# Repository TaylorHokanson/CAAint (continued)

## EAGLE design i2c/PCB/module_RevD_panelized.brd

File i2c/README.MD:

### Attiny Breakout Hello World

1. Populate breakout board with components:

   - Attiny85
   - 2 x 3mm LEDs
   - 2 x 270ohm resistors
   - male pin headers
   - [.1 uf capacitor](https://www.mouser.com/ProductDetail/Murata-Electronics/RDER71H104K0P1H03B?qs=sGAEpiMZZMukHu%252bjC5l7YWXRuVs7xNwsPrUM%2fIYCMaY%3d) <-- important!
2. Attach [AVR programmer](https://www.sparkfun.com/products/9825) to breakout (taking careful note of plug polarity, see breakout silkscreen for orientation).
3. Select "power device" on programmer via switch.
4. Connect programmer to computer via USB
5. Download and install [board definitions](https://github.com/damellis/attiny) for Attiny
6. Set the following in the Arduino IDE Tools menu:

   - Board: Attiny 25/45/85
   - Processor: Attiny85
   - Clock: 1Mhz
   - Port: Leave this blank
   - Programmer: USBTinyISP
7. Arduino IDE > Tools > Burn Bootloader

   - Only needs to be done once per chip
8. Change Clock to 8mhz internal.
8. Upload [attiny_hello_world.ino](Code/) with the same settings as above.
9. If all goes well, this will flash the second LED on the breakout.

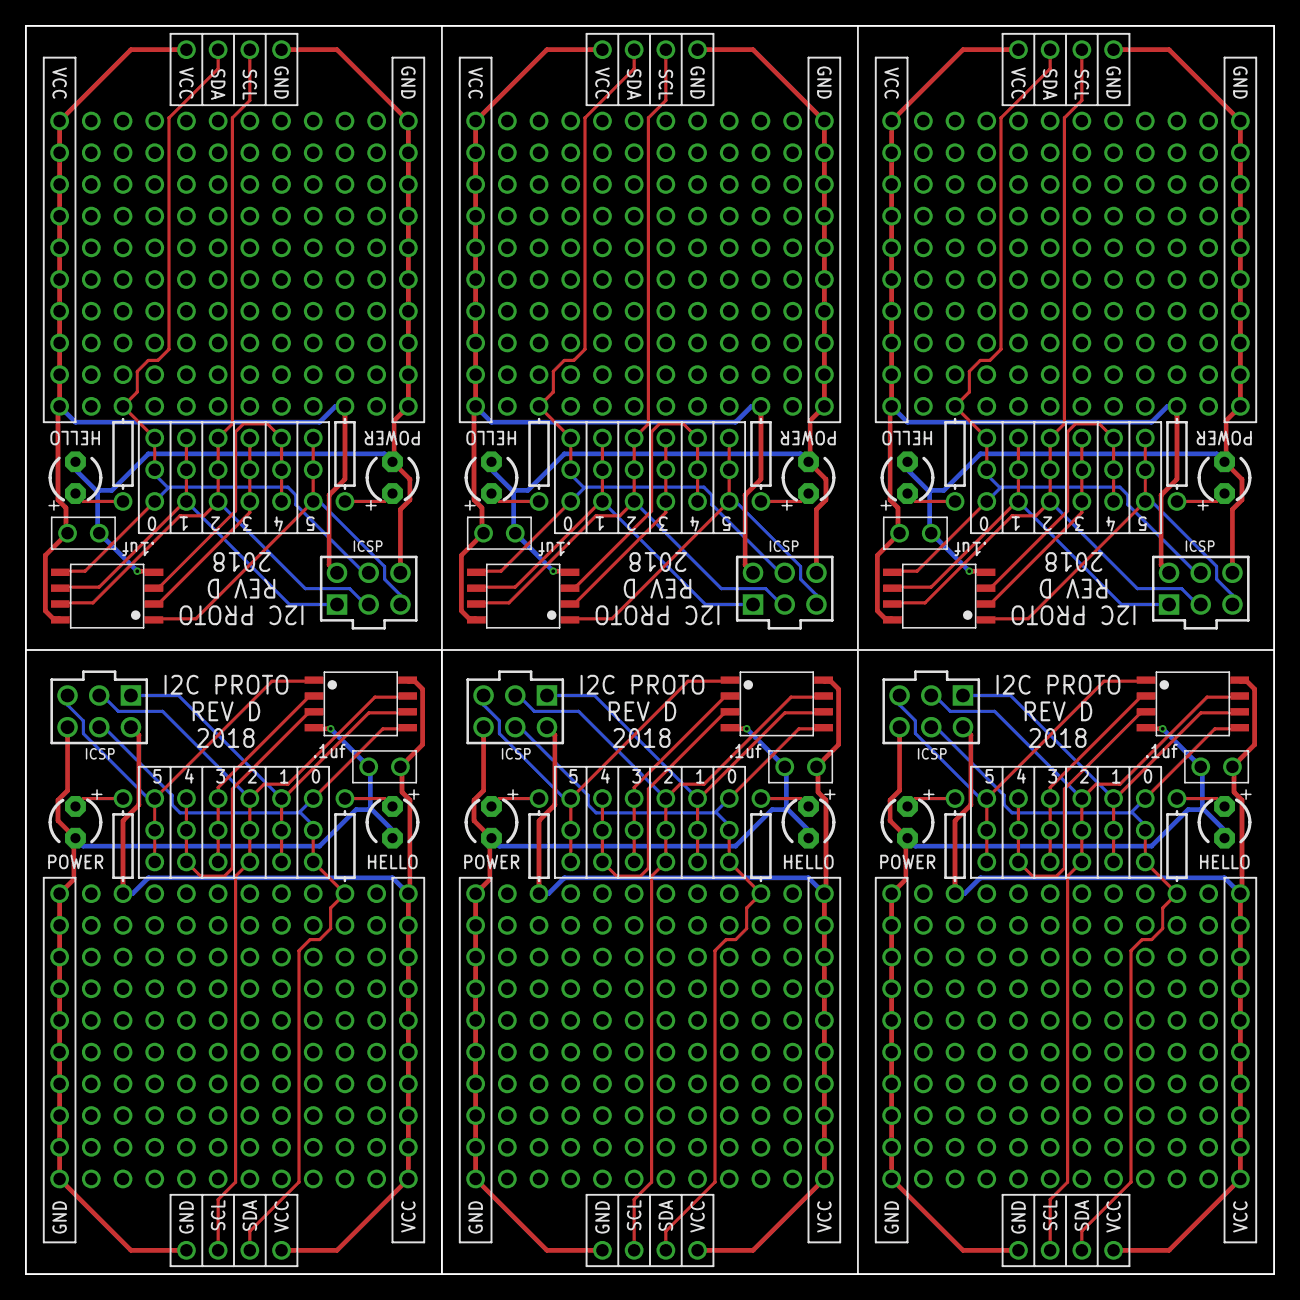
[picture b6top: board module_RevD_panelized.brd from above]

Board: 2 copper layers, 100.0 x 100.0 mm, 882 parts (0 on the bottom side), 60 nets.

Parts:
HELLO, HELLO1, HELLO2, HELLO3, HELLO4, HELLO5: LED3MM
IC1, IC2, IC3, IC4, IC5, IC6: ATTINY85-20SU; SOT127P798X216-8N
J1, J2, J3, J4, J5, J6: M20-9980346; HDRV6W64P254_2X3_762X508X868P
POWER, POWER1, POWER2, POWER3, POWER4, POWER5: LED3MM
U$1, U$2, U$3, U$4, U$5, U$6, U$7, U$8, U$9, U$10, U$11, U$12, U$13, U$14, U$15, U$16, U$17, U$18, U$19, U$20, U$21, U$22, U$23, U$24, U$25, U$26, U$27, U$28, U$29, U$30, U$31, U$32, U$33, U$34, U$35, U$36, U$37, U$38, U$39, U$40, U$41, U$42, U$43, U$44, U$45, U$46, U$47, U$48, U$49, U$50, U$51, U$52, U$53, U$54, U$55, U$56, U$57, U$58, U$59, U$60, U$61, U$62, U$63, U$64, U$65, U$66, U$67, U$68, U$69, U$70, U$75, U$76, U$77, U$78, U$79, U$80, U$81, U$82, U$83, U$84, U$85, U$86, U$87, U$88, U$89, U$90, U$91, U$92, U$93, U$94, U$95, U$96, U$97, U$98, U$99, U$100, U$101, U$102, U$103, U$104, U$105, U$106, U$107, U$108, U$109, U$110, U$111, U$112, U$113, U$114, U$115, U$116, U$117, U$118, U$119, U$120, U$121, U$122, U$124, U$125, U$128, U$129, U$130, U$131, U$132, U$133, U$134, U$135, U$136, U$137, U$138, U$139, U$140, U$141, U$142, U$143, U$144, U$145, U$146, U$147, U$148, U$149, U$150, U$151, U$152, U$153, U$154, U$155, U$156, U$157, U$158, U$159, U$160, U$161, U$162, U$163, U$164, U$165, U$166, U$167, U$168, U$169, U$170, U$171, U$172, U$173, U$174, U$175, U$176, U$177, U$178, U$179, U$180, U$181, U$182, U$183, U$184, U$185, U$186, U$187, U$188, U$189, U$190, U$191, U$192, U$193, U$194, U$195, U$196, U$197, U$198, U$199, U$200, U$201, U$202, U$203, U$204, U$205, U$206, U$207, U$208, U$209, U$210, U$211, U$212, U$213, U$218, U$219, U$220, U$221, U$222, U$223, U$224, U$225, U$226, U$227, U$228, U$229, U$230, U$231, U$232, U$233, U$234, U$235, U$236, U$237, U$238, U$239, U$240, U$241, U$242, U$243, U$244, U$245, U$246, U$247, U$248, U$249, U$250, U$251, U$252, U$253, U$254, U$255, U$256, U$257, U$258, U$259, U$260, U$261, U$262, U$263, U$267, U$268, U$269, U$270, U$271, U$272, U$273, U$274, U$275, U$276, U$277, U$278, U$279, U$280, U$281, U$282, U$283, U$284, U$285, U$286, U$287, U$288, U$289, U$290, U$291, U$292, U$293, U$294, U$295, U$296, U$297, U$298, U$299, U$300, U$301, U$302, U$303, U$304, U$305, U$306, U$307, U$308, U$309, U$310, U$311, U$312, U$313, U$314, U$315, U$316, U$317, U$318, U$319, U$320, U$321, U$322, U$323, U$324, U$325, U$326, U$327, U$328, U$329, U$330, U$331, U$332, U$333, U$334, U$335, U$336, U$337, U$338, U$339, U$340, U$341, U$342, U$343, U$344, U$345, U$346, U$347, U$348, U$349, U$350, U$351, U$352, U$353, U$354, U$355, U$356, U$361, U$362, U$363, U$364, U$365, U$366, U$367, U$368, U$369, U$370, U$371, U$372, U$373, U$374, U$375, U$376, U$377, U$378, U$379, U$380, U$381, U$382, U$383, U$384, U$385, U$386, U$387, U$388, U$389, U$390, U$391, U$392, U$393, U$394, U$395, U$396, U$397, U$398, U$399, U$400, U$401, U$402, U$403, U$404, U$405, U$406, U$410, U$411, U$412, U$413, U$414, U$415, U$416, U$417, U$418, U$419, U$420, U$421, U$422, U$423, U$424, U$425, U$426, U$427, U$428, U$429, U$430, U$431, U$432, U$433, U$434, U$435, U$436, U$437, U$438, U$439, U$440, U$441, U$442, U$443, U$444, U$445, U$446, U$447, U$448, U$449, U$450, U$451, U$452, U$453, U$454, U$455, U$456, U$457, U$458, U$459, U$460, U$461, U$462, U$463, U$464, U$465, U$466, U$467, U$468, U$469, U$470, U$471, U$472, U$473, U$474, U$475, U$476, U$477, U$478, U$479, U$480, U$481, U$482, U$483, U$484, U$485, U$486, U$487, U$488, U$489, U$490, U$491, U$492, U$493, U$494, U$495, U$496, U$497, U$498, U$499, U$504, U$505, U$506, U$507, U$508, U$509, U$510, U$511, U$512, U$513, U$514, U$515, U$516, U$517, U$518, U$519, U$520, U$521, U$522, U$523, U$524, U$525, U$526, U$527, U$528, U$529, U$530, U$531, U$532, U$533, U$534, U$535, U$536, U$537, U$538, U$539, U$540, U$541, U$542, U$543, U$544, U$545, U$546, U$547, U$548, U$549, U$553, U$554, U$555, U$556, U$557, U$558, U$559, U$560, U$561, U$562, U$563, U$564, U$565, U$566, U$567, U$568, U$569, U$570, U$571, U$572, U$573, U$574, U$575, U$576, U$577, U$578, U$579, U$580, U$581, U$582, U$583, U$584, U$585, U$586, U$587, U$588, U$589, U$590, U$591, U$592, U$593, U$594, U$595, U$596, U$597, U$598, U$599, U$600, U$601, U$602, U$603, U$604, U$605, U$606, U$607, U$608, U$609, U$610, U$611, U$612, U$613, U$614, U$615, U$616, U$617, U$618, U$619, U$620, U$621, U$622, U$623, U$624, U$625, U$626, U$627, U$628, U$629, U$630, U$631, U$632, U$633, U$634, U$635, U$636, U$637, U$638, U$639, U$640, U$641, U$642, U$647, U$648, U$649, U$650, U$651, U$652, U$653, U$654, U$655, U$656, U$657, U$658, U$659, U$660, U$661, U$662, U$663, U$664, U$665, U$666, U$667, U$668, U$669, U$670, U$671, U$672, U$673, U$674, U$675, U$676, U$677, U$678, U$679, U$680, U$681, U$682, U$683, U$684, U$685, U$686, U$687, U$688, U$689, U$690, U$691, U$692, U$696, U$697, U$698, U$699, U$700, U$701, U$702, U$703, U$704, U$705, U$706, U$707, U$708, U$709, U$710, U$711, U$712, U$713, U$714, U$715, U$716, U$717, U$718, U$719, U$720, U$721, U$722, U$723, U$724, U$725, U$726, U$727, U$728, U$729, U$730, U$731, U$732, U$733, U$734, U$735, U$736, U$737, U$738, U$739, U$740, U$741, U$742, U$743, U$744, U$745, U$746, U$747, U$748, U$749, U$750, U$751, U$752, U$753, U$754, U$755, U$756, U$757, U$758, U$759, U$760, U$761, U$762, U$763, U$764, U$765, U$766, U$767, U$768, U$769, U$770, U$771, U$772, U$773, U$774, U$775, U$776, U$777, U$778, U$779, U$780, U$781, U$782, U$783, U$784, U$785, U$790, U$791, U$792, U$793, U$794, U$795, U$796, U$797, U$798, U$799, U$800, U$801, U$802, U$803, U$804, U$805, U$806, U$807, U$808, U$809, U$810, U$811, U$812, U$813, U$814, U$815, U$816, U$817, U$818, U$819, U$820, U$821, U$822, U$823, U$824, U$825, U$826, U$827, U$828, U$829, U$830, U$831, U$832, U$833, U$834, U$835, U$839, U$840, U$841, U$842, U$843, U$844, U$845, U$846, U$847, U$848, U$849, U$850, U$851, U$852, U$853, U$854, U$855, U$856, U$857, U$858: ONE_PAD; 1X01
U$71, U$214, U$357, U$500, U$643, U$786: GND; 1X01
U$72, U$216, U$359, U$502, U$645, U$788: SDA; 1X01
U$73, U$217, U$360, U$503, U$646, U$789: SCL; 1X01
U$74, U$215, U$358, U$501, U$644, U$787: VCC; 1X01
U$123, U$264, U$407, U$550, U$693, U$836: DECOUPLING_CAP
U$126, U$127, U$265, U$266, U$408, U$409, U$551, U$552, U$694, U$695, U$837, U$838: RESISTOR; AXIAL-0.3

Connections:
GND: HELLO.NEG, IC1.GND, J1.GND, POWER.NEG, U$71.P$1, U$99.P$1, U$100.P$1, U$123.P$1, U$124.P$1, U$125.P$1, U$128.P$1, U$129.P$1, U$130.P$1, U$131.P$1, U$132.P$1, U$133.P$1
GND1: HELLO1.NEG, IC2.GND, J2.GND, POWER1.NEG, U$214.P$1, U$264.P$1, U$267.P$1, U$268.P$1, U$269.P$1, U$270.P$1, U$271.P$1, U$272.P$1, U$273.P$1, U$274.P$1, U$275.P$1, U$276.P$1
GND2: HELLO2.NEG, IC3.GND, J3.GND, POWER2.NEG, U$357.P$1, U$407.P$1, U$410.P$1, U$411.P$1, U$412.P$1, U$413.P$1, U$414.P$1, U$415.P$1, U$416.P$1, U$417.P$1, U$418.P$1, U$419.P$1
GND3: HELLO3.NEG, IC4.GND, J4.GND, POWER3.NEG, U$500.P$1, U$550.P$1, U$553.P$1, U$554.P$1, U$555.P$1, U$556.P$1, U$557.P$1, U$558.P$1, U$559.P$1, U$560.P$1, U$561.P$1, U$562.P$1
GND6: HELLO4.NEG, IC5.GND, J5.GND, POWER4.NEG, U$643.P$1, U$693.P$1, U$696.P$1, U$697.P$1, U$698.P$1, U$699.P$1, U$700.P$1, U$701.P$1, U$702.P$1, U$703.P$1, U$704.P$1, U$705.P$1
GND7: HELLO5.NEG, IC6.GND, J6.GND, POWER5.NEG, U$786.P$1, U$836.P$1, U$839.P$1, U$840.P$1, U$841.P$1, U$842.P$1, U$843.P$1, U$844.P$1, U$845.P$1, U$846.P$1, U$847.P$1, U$848.P$1
unnamed: POWER.POS, U$126.P$3
unnamed: HELLO.POS, U$127.P$3
unnamed: POWER1.POS, U$265.P$3
unnamed: HELLO1.POS, U$266.P$3
unnamed: POWER2.POS, U$408.P$3
unnamed: HELLO2.POS, U$409.P$3
unnamed: POWER3.POS, U$551.P$3
unnamed: HELLO3.POS, U$552.P$3
unnamed: POWER4.POS, U$694.P$3
unnamed: HELLO4.POS, U$695.P$3
unnamed: POWER5.POS, U$837.P$3
unnamed: HELLO5.POS, U$838.P$3
PB0: IC1.PB0, J1.0/MOSI/SDA, U$72.P$1, U$75.P$1, U$76.P$1, U$77.P$1, U$127.P$4
PB1: IC1.PB1, J1.1/MISO, U$78.P$1, U$79.P$1, U$80.P$1
PB2: IC1.PB2, J1.2/SCK/SCL, U$73.P$1, U$81.P$1, U$82.P$1, U$83.P$1
PB3: IC1.PB3, U$84.P$1, U$85.P$1, U$86.P$1
PB4: IC1.PB4, U$87.P$1, U$88.P$1, U$89.P$1
PB5: IC1.PB5, J1.5/RST, U$90.P$1, U$91.P$1, U$92.P$1
PB6: IC2.PB0, J2.0/MOSI/SDA, U$216.P$1, U$218.P$1, U$219.P$1, U$220.P$1, U$266.P$4
PB7: IC2.PB3, U$227.P$1, U$228.P$1, U$229.P$1
PB8: IC2.PB4, U$230.P$1, U$231.P$1, U$232.P$1
PB9: IC2.PB2, J2.2/SCK/SCL, U$217.P$1, U$224.P$1, U$225.P$1, U$226.P$1
PB10: IC2.PB5, J2.5/RST, U$233.P$1, U$234.P$1, U$235.P$1
PB11: IC2.PB1, J2.1/MISO, U$221.P$1, U$222.P$1, U$223.P$1
PB12: IC3.PB0, J3.0/MOSI/SDA, U$359.P$1, U$361.P$1, U$362.P$1, U$363.P$1, U$409.P$4
PB13: IC3.PB3, U$370.P$1, U$371.P$1, U$372.P$1
PB14: IC3.PB4, U$373.P$1, U$374.P$1, U$375.P$1
PB15: IC3.PB2, J3.2/SCK/SCL, U$360.P$1, U$367.P$1, U$368.P$1, U$369.P$1
PB16: IC3.PB5, J3.5/RST, U$376.P$1, U$377.P$1, U$378.P$1
PB17: IC3.PB1, J3.1/MISO, U$364.P$1, U$365.P$1, U$366.P$1
PB18: IC4.PB0, J4.0/MOSI/SDA, U$502.P$1, U$504.P$1, U$505.P$1, U$506.P$1, U$552.P$4
PB19: IC4.PB3, U$513.P$1, U$514.P$1, U$515.P$1
PB20: IC4.PB4, U$516.P$1, U$517.P$1, U$518.P$1
PB21: IC4.PB2, J4.2/SCK/SCL, U$503.P$1, U$510.P$1, U$511.P$1, U$512.P$1
PB22: IC4.PB5, J4.5/RST, U$519.P$1, U$520.P$1, U$521.P$1
PB23: IC4.PB1, J4.1/MISO, U$507.P$1, U$508.P$1, U$509.P$1
PB24: IC5.PB0, J5.0/MOSI/SDA, U$645.P$1, U$647.P$1, U$648.P$1, U$649.P$1, U$695.P$4
PB25: IC5.PB3, U$656.P$1, U$657.P$1, U$658.P$1
PB26: IC5.PB4, U$659.P$1, U$660.P$1, U$661.P$1
PB27: IC5.PB2, J5.2/SCK/SCL, U$646.P$1, U$653.P$1, U$654.P$1, U$655.P$1
PB30: IC5.PB5, J5.5/RST, U$662.P$1, U$663.P$1, U$664.P$1
PB31: IC5.PB1, J5.1/MISO, U$650.P$1, U$651.P$1, U$652.P$1
PB32: IC6.PB0, J6.0/MOSI/SDA, U$788.P$1, U$790.P$1, U$791.P$1, U$792.P$1, U$838.P$4
PB33: IC6.PB3, U$799.P$1, U$800.P$1, U$801.P$1
PB36: IC6.PB4, U$802.P$1, U$803.P$1, U$804.P$1
PB37: IC6.PB2, J6.2/SCK/SCL, U$789.P$1, U$796.P$1, U$797.P$1, U$798.P$1
PB38: IC6.PB5, J6.5/RST, U$805.P$1, U$806.P$1, U$807.P$1
PB39: IC6.PB1, J6.1/MISO, U$793.P$1, U$794.P$1, U$795.P$1
VCC: IC1.VCC, J1.VCC, U$74.P$1, U$123.P$2, U$126.P$4, U$134.P$1, U$135.P$1, U$136.P$1, U$137.P$1, U$138.P$1, U$139.P$1, U$140.P$1, U$141.P$1, U$142.P$1, U$143.P$1
VCC1: IC2.VCC, J2.VCC, U$215.P$1, U$264.P$2, U$265.P$4, U$277.P$1, U$278.P$1, U$279.P$1, U$280.P$1, U$281.P$1, U$282.P$1, U$283.P$1, U$284.P$1, U$285.P$1, U$286.P$1
VCC2: IC3.VCC, J3.VCC, U$358.P$1, U$407.P$2, U$408.P$4, U$420.P$1, U$421.P$1, U$422.P$1, U$423.P$1, U$424.P$1, U$425.P$1, U$426.P$1, U$427.P$1, U$428.P$1, U$429.P$1
VCC3: IC4.VCC, J4.VCC, U$501.P$1, U$550.P$2, U$551.P$4, U$563.P$1, U$564.P$1, U$565.P$1, U$566.P$1, U$567.P$1, U$568.P$1, U$569.P$1, U$570.P$1, U$571.P$1, U$572.P$1
VCC4: IC5.VCC, J5.VCC, U$644.P$1, U$693.P$2, U$694.P$4, U$706.P$1, U$707.P$1, U$708.P$1, U$709.P$1, U$710.P$1, U$711.P$1, U$712.P$1, U$713.P$1, U$714.P$1, U$715.P$1
VCC5: IC6.VCC, J6.VCC, U$787.P$1, U$836.P$2, U$837.P$4, U$849.P$1, U$850.P$1, U$851.P$1, U$852.P$1, U$853.P$1, U$854.P$1, U$855.P$1, U$856.P$1, U$857.P$1, U$858.P$1

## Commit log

2017-10-02 ideas
2017-10-02 added links
2017-10-02 more linkzzz
2017-10-02 linkzzz
2017-10-02 gotchas
2017-10-05 updatezzz
2017-10-05 words
2017-10-06 Sierra troubleshooting
2017-10-06 Added sample sketch
2017-10-06 more words
2017-10-07 Added Fritzing Folder
2017-10-07 added hellomesh_oled
2017-10-08 got it working
    Now the display messages reflect the ID of the external ESP chip.
2017-10-08 add ESP reference link
2017-10-12 Firmware flashing notes
2017-10-12 Removed wip ino
2017-10-12 more notes
2017-10-12 Added hellomesh example 2
2017-10-17 note on delays
2017-10-17 README
2017-10-17 shipping costs
2017-10-17 notes
2017-10-18 tracking network nodes
2017-10-25 anchor
2017-10-25 readme updates
2017-10-25 added PCB section
2017-10-25 added PCB files
2017-10-26 battery info
2017-11-29 added file
2017-11-29 Rename PCB.md to README.md
2017-11-29 housekeeping
2017-11-29 upload
2017-11-29 added image
2017-11-29 changed image size
2017-11-29 bleh
2017-11-29 deleted funky links
2017-11-29 added dip info
2018-01-08 Added Heltec Automation Wifi Kit 32 footprint
2018-01-10 Added breakout board/badge rev A
2018-01-20 Fixed footprint and naming on Heltec ESP32
2018-01-22 BOM updates
2018-01-29 added ESP32 protobadge test
2018-01-29 Added folder, library comments
2018-03-31 reorganizing
2018-03-31 reorg
2018-03-31 added Media folder
2018-04-02 added TTGO-ESP32-OLED part to library
2018-04-02 corrected pin spacing on TTGO board device
2018-04-26 Added new BadgeParts to eagle lib
2018-04-26 added herm connector
2018-04-26 fixed orientation of herm conn
2018-04-26 added buzzer ino
2018-04-26 speaker support
2018-04-27 added factory firmware for TTGO board
2018-04-27 syntax update
2018-05-01 added OLED example
2018-05-01 added example with DS18B20 sensor
2018-05-02 syntax correction and font change
2018-05-03 incorporated onboard led to example
2018-05-04 added ambient light sensor to library
2018-05-04 added 5-way tac
2018-05-06 initial RevA design
2018-05-07 PCB rev B
2018-05-08 added i2c Eagle project
2018-05-10 Added ESP menu example
2018-05-13 ino updates
2018-05-13 Improved OLED feedback
2018-05-13 Added cap touch
2018-05-15 stuff
2018-05-15 determined that pins 0 and 2 should not be used as I/O
2018-05-18 rev C design added and update to library
2018-05-30 corrected capsense pads
2018-06-01 corrected footprint on 5-way tac switch
2018-06-01 changed pin assignments for RevC support
2018-06-01 added master and slave code for bare TTGO w oled
2018-06-03 avoiding no-no pins
2018-06-03 rev d changes and notes
2018-06-03 rev d added
2018-06-03 reroute RevD
2018-06-03 joystick footprint correction
2018-06-03 corrected herm connect
2018-06-04 RevE WIP
2018-06-04 Rhino layout
2018-06-04 housekeeping, revE WIP
    don't forget to copy over the lbr into the correct location on your computer
2018-06-07 RevE off to fab house!
2018-06-08 reorg, i2c dev, lbr updates
2018-06-09 made two hema defs
    To account for flipping
2018-06-10 i2c, lbr updates
2018-06-11 added hema vanilla and dp proto
2018-06-11 PCB design/lib updates
2018-06-13 new artwork test for i2c modules
2018-06-14 vector artwork added
2018-06-14 first i2c dongle iteration panelized
2018-06-21 support for RevE board
    Flipping the display and changing of pinouts for switch
2018-06-21 updated for revE
2018-06-22 example for buzzer on RevE
2018-06-22 Merged GND traces to create RevF
2018-06-26 updated TTGO battery clearance (+2mm)
2018-06-26 added capsense def back in
2018-06-26 round capsense buttons
2018-06-27 updated net classes
2018-06-27 Fixed bug in tac button package def
2018-06-27 moved TTGO silk to tdocu
2018-06-27 updated hema definition
2018-06-27 visual library part cleanup
2018-07-01 added documentation of RevE
2018-07-03 fixed hema silkscreen issue
2018-07-03 updated battery hole, removed TTGO mounts for clearance
2018-07-11 fixed ICSP, added module rev B
2018-07-20 added decoupling cap to VCC/GND line
2018-07-20 Added a comment regarding port problems
2018-07-20 separated pin breakouts in silkscreen
2018-07-20 updated LED definition
2018-07-23 swapped hema for 4p header; connect HW to D0, docu
2018-07-24 trying to pack in more proto area WIP
2018-07-25 added i2c rev C
2018-07-26 updated brd tsilk and added bitly link on bsilk, routed for SEEED
2018-07-26 compulsive text alignment
2018-07-26 fixed duplicate RST reference in ICSP definition
2018-07-27 SCH visual layout
2018-07-27 I2C RevC Panelized
2018-07-27 i2c rev c panel submitted for mfg
2018-08-02 added attiny hello world
2018-08-02 i2c revD PCB
2018-08-03 smaller proto pads, improved routing
2018-08-06 updated rev D panelizaiton files
2018-08-09 Rework of revD boards
2018-08-20 added ttgo shield rev g
2018-08-20 revH exchanges hema i2c for right angle female header
2018-08-20 updated capsense buttons to clear oshpark drc
2018-08-26 added silk flavor text
2018-08-26 added rear silk overworld
2018-08-26 corrected bsilk scaling and masking
2018-08-28 OSHpark gerbers rev H
2018-09-04 copied ttgo master/slave espnow code out of archive
2018-09-13 housecleaning
2018-09-14 added one line to fix -2 devices error
2018-09-27 esp now new example
2018-09-27 added correction to delay
    changed delay on master code and corrected polarity on slave led
2018-09-30 fixed weird buffer issues
2018-10-03 restored onboard LED flash
2018-10-03 not sure why this doesn't work
2018-10-05 blink example added for rev H board
2018-10-11 added iteration for display and shield LEDs
2018-10-11 Update TTGO/Code/Basic Functions/Blink/README
2018-10-11 added buzz example
2018-11-15 started in on the NMC design
2018-11-15 more research
2018-11-15 nmc research
2018-12-04 NMC show updates
2018-12-18 big push
2018-12-18 added SMT battery mount to lbr
2018-12-18 added smt battery mount
2018-12-19 Change dim to meet seeed rqmts
2018-12-19 added lanyard hole, 3 RGB LEDs
2018-12-19 breathing room for redesign
2018-12-19 added SMT switch to design/lbr
    This can be used as on/off for battery, but should also be wired to isolate battery voltage from USB
2018-12-19 added through hole CR battery holder to lbr
2018-12-20 updated SMT switch
2018-12-20 updated lbr, proto area simplified
2018-12-20 lbr updates, proto area con't
2018-12-20 recentered origin
2018-12-20 cleanup con't
2018-12-20 added PB B/Os to proto grid
2018-12-20 custom RGB LED def includes .1uf cap in layout
2018-12-20 fixed battery orientation
2018-12-20 Isolated battery/USB power supplies at switch
2018-12-21 Rename A Designer's Guide to Lithium Ion (Li-ion) Battery Charging | DigiKey.webloc to A Designer's Guide to Lithium Ion (Li-ion) Battery Charging DigiKey.webloc
2018-12-21 Rename LIR2032 Coin Cell Charger | Hackaday.io.webloc to LIR2032 Coin Cell Charger Hackaday.io.webloc
2018-12-21 four panel pcb design with snap apart tabs v1
2018-12-21 Roll back to boring profile
2018-12-21 restored most parts to layout
2018-12-21 all together now
2018-12-21 aligning parts
2018-12-21 Added VBAT to net classes
2018-12-21 working lbr errors in drc
2018-12-21 added OSHpark logo to main board
    variant also added for later work
2018-12-21 Organizing fabrication files
2018-12-21 not sure, hope this doesn't break stuff
2018-12-21 updated smt battery silk
2018-12-21 working OSH panelize file
2018-12-21 Finalized file for OSH
2018-12-23 Stencil stuff
2019-01-15 adjusted silk, moved T-hole LEDs away from RGBs
2019-01-15 nmc2 panelized for seeed
2019-01-16 added organic layout
2019-01-20 added pacman board WIP
2019-01-20 added silk outline, mirrored battery parts
2019-01-21 visual improvements, replaced cap w/ surface mount
2019-01-21 added OSH silk
2019-01-24 more pacman updates
2019-02-15 Update pacman_barblink.ino
    corrected syntax
2019-09-03 Added NMC Border Control Design
2019-09-05 corrected polarity
2019-09-14 added decoupling cap to pcb
2019-09-15 added revB firmware and changed battery holder orientation
